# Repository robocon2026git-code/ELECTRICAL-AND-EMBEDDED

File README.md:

\# GITHUB WORKFLOW GUIDE

Welcome to \*\*ROBOCON WORKSPACE\*\*

This document explains \*\*how team members should clone the repo, set up Git, and work using feature branches\*\*.

⚠️ Direct changes to `main` are NOT allowed.  

All work must be done using \*\*feature branches\*\* and merged via \*\*Pull Requests (PRs)\*\*.

---

\## 🧠 Git Basics (Quick Understanding)

\- \*\*Repository (repo)\*\* → Project stored with version control

\- \*\*main branch\*\* → Stable, reviewed code only

\- \*\*feature branch\*\* → Your personal workspace

\- \*\*commit\*\* → A saved snapshot of changes

\- \*\*origin\*\* → Remote GitHub repository

\- \*\*Pull Request (PR)\*\* → Request to merge code into `main`

---

\## One-Time Setup (Required on Every New PC)

Run these commands \*\*once\*\* after installing Git:

```bash

git config --global user.name "Your Name"

git config --global user.email "your-email@example.com"

git config --global init.defaultBranch main

\## To verify configuration

git config --global --list

**## Cloning and work steps starts from here:**

!!!!IMPORTANT ONE TIME SETTING AFTER INSTALLED GIT:

git clone https://github.com/robocon2026git-code/ELECTRICAL-AND-EMBEDDED.git

# \## REGULAR WORK PROCEDURE

1)cd ELECTRO-CORE

2)git status

3)git checkout main					//This line says go to main branch

4)git pull origin main					//Important step otherwise you might miss some files that was updated recently

5)git checkout -b feature/short-description		//Creating your local workspace

    ex:

        git checkout -b feature/pneumatic\_actuation

	git checkout -b feature/arduino-motor

	git checkout -b feature/i2c-driver

After work done run this command once

6)git status

\## THE FOLLOWING STEPS ARE AFTER COMPLETION OF YOUR WORK

\*\* THIS THREE COMMENTS WE WILL USE FREQUENTLY

7)git add .

8)git commit -m "Added new functionality to drive train"

Run this command only when your first push after creation of your feature branch

9) a_)git push -u origin feature/your-branch-name

from next push onwards you can just type

   b_)git push

For local space

10) a_)git branch -d feature/your-branch-name		//Run this comment only after code is merged. This will delete your branch

For remote space

    b_)git push origin --delete feature/your-branch-name

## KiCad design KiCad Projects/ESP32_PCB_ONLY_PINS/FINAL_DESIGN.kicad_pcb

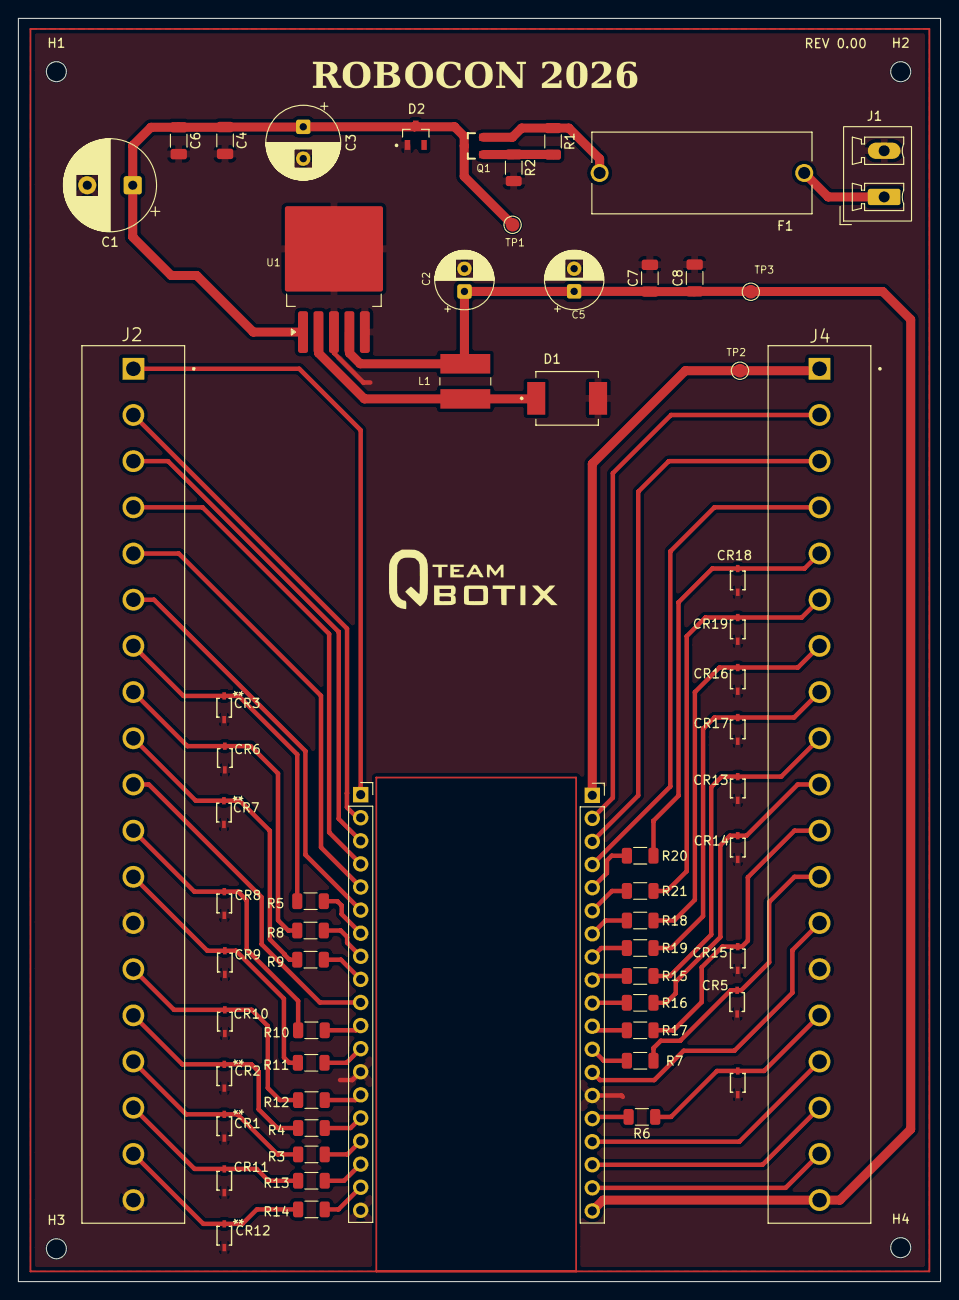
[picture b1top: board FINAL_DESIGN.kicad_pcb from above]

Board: 2 copper layers, 101.4 x 138.9 mm, 66 parts (0 on the bottom side), 60 nets.

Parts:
C1: 680uF; CP_Radial_D10.0mm_P5.00mm
C2, C5: 220uF; CP_Radial_D6.3mm_P2.50mm
C3: 470uF; CP_Radial_D8.0mm_P3.50mm
C4, C7: 10uF; C_1206_3216Metric
C6, C8: 0.1uF; C_1206_3216Metric
CR1, CR2, CR3, CR4, CR5, CR6, CR7, CR8, CR9, CR10, CR11, CR12, CR13, CR14, CR15, CR16, CR17, CR18, CR19: PESD3V3L1BA_115; DIODE_PESD3V3L1BA_115_NEX
D1: SS34; DIO_SS34
D2: MMBZ5242B-7-F; SOT91P240X102-3N
F1: 4628; FUSE_4628
H1, H2, H3, H4: MountingHole_2.2mm_M2
J1: Screw_Terminal_01x02; PhoenixContact_MCV_1,5_2-G-5.08_1x02_P5.08mm_Vertical
J2, J4: TB010-508-P19BK; CUI_TB010-508-P19BK
J3, J5: Conn_01x19_Socket; PinSocket_1x19_P2.54mm_Vertical
L1: WE-PD2_4532; L_Wuerth_WE-PD2-Typ-MS
Q1: AO3401A; SOT23-3
R1, R2: 100K; R_1206_3216Metric
R3, R4: 33; R_1206_3216Metric
R5, R6, R7, R8, R9, R10, R11, R12, R13, R14, R15, R16, R17, R18, R19, R20, R21: 100; R_1206_3216Metric
TP1: 12V; TestPoint_Pad_D1.5mm
TP2: 3V3; TestPoint_Pad_D1.5mm
TP3: 5V; TestPoint_Pad_D1.5mm
U1: LM2596S-5; TO-263-5_TabPin3

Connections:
+3V3: J4.1, J5.1, TP2.1 (1_1)
/12V: C1.1, C3.1, C4.1, C6.1, D2.3, Q1.3, TP1.1 (1_1), U1.1 (VIN)
CLK: J2.1, J3.1
CMD: J4.18, J5.18
EN: J4.2, J5.2
GND: C1.2, C2.2, C3.2, C4.2, C5.2, C6.2, C7.2, C8.2, CR1.2, CR2.2, CR3.2, CR4.2, CR5.2, CR6.2, CR7.2, CR8.2, CR9.2, CR10.2, CR11.2, CR12.2, CR13.2, CR14.2, CR15.2, CR16.2, CR17.2, CR18.2, CR19.2, D1.A, D2.1, J1.2, J2.13, J2.19, J3.13, J3.19, J4.14, J5.14, R2.2, U1.3 (GND), U1.5 (~ON/OFF)
IO_1: J3.16, R3.2
IO_3: J3.15, R4.2
IO_4: J3.7, R5.2
IO_13: J5.15, R6.2
IO_14: J5.12, R7.2
IO_16: J3.8, R8.2
IO_17: J3.9, R9.2
IO_18: J3.11, R10.2
IO_19: J3.12, R11.2
IO_21: J3.14, R12.2
IO_22: J3.17, R13.2
IO_23: J3.18, R14.2
IO_25: J5.9, R15.2
IO_26: J5.10, R16.2
IO_27: J5.11, R17.2
IO_32: J5.7, R18.2
IO_33: J5.8, R19.2
IO_34: J5.5, R20.2
IO_35: J5.6, R21.2
I/O_0: J2.6, J3.6
I/O_2: J2.5, J3.5
I/O_4: CR3.1, J2.7, R5.1
I/O_5: J2.10, J3.10
I/O_12: J4.13, J5.13
I/O_13: CR4.1, J4.15, R6.1
I/O_14: CR5.1, J4.12, R7.1
I/O_15: J2.4, J3.4
I/O_16: CR6.1, J2.8, R8.1
I/O_17: CR7.1, J2.9, R9.1
I/O_18: CR8.1, J2.11, R10.1
I/O_19: CR9.1, J2.12, R11.1
I/O_21: CR10.1, J2.14, R12.1
I/O_22: CR11.1, J2.17, R13.1
I/O_23: CR12.1, J2.18, R14.1
I/O_25: CR13.1, J4.9, R15.1
I/O_26: CR14.1, J4.10, R16.1
I/O_27: CR15.1, J4.11, R17.1
I/O_32: CR16.1, J4.7, R18.1
I/O_33: CR17.1, J4.8, R19.1
I/O_34: CR18.1, J4.5, R20.1
I/O_35: CR19.1, J4.6, R21.1
unnamed: F1.2, Q1.2, R1.1
unnamed: F1.1, J1.1
unnamed: Q1.1, R1.2, R2.1
unnamed: D1.C, L1.1, U1.2 (OUT)
RXD: CR2.1, J2.15, R4.1
SD0: J2.2, J3.2
SD1: J2.3, J3.3
SD2: J4.16, J5.16
SD3: J4.17, J5.17
SN: J4.4, J5.4
SP: J4.3, J5.3
TXD: CR1.1, J2.16, R3.1
VIN 5V: C2.1, C5.1, C7.1, C8.1, J4.19, J5.19, L1.2, TP3.1 (1_1), U1.4 (FB)

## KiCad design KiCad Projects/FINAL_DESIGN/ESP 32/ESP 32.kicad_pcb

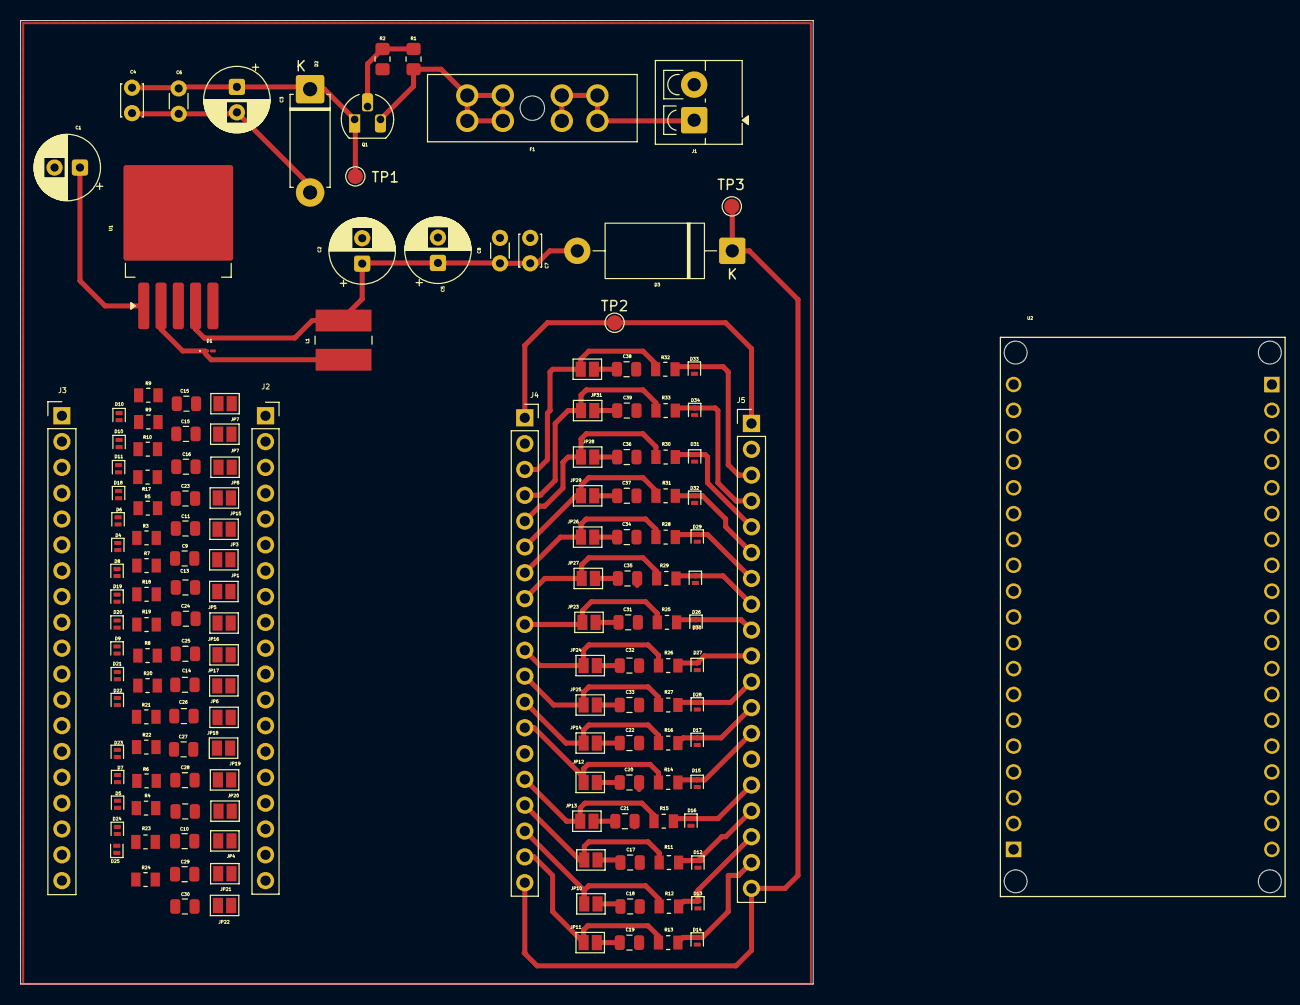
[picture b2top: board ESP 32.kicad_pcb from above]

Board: 2 copper layers, 78.0 x 94.7 mm, 154 parts (0 on the bottom side), 105 nets.

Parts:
C1: 680uF; CP_Radial_D6.3mm_P2.50mm
C2, C5: 220uF; CP_Radial_D6.3mm_P2.50mm
C3: 470uF; CP_Radial_D6.3mm_P2.50mm
C4, C7: 10uF; C_Disc_D3.0mm_W2.0mm_P2.50mm
C6, C8: 0.1uF; C_Disc_D3.0mm_W1.6mm_P2.50mm
C9, C10, C11, C12, C13, C14, C15, C15#2, C16, C17, C18, C19, C20, C21, C22, C23, C24, C25, C26, C27, C28, C29, C30, C31, C32, C33, C34, C35, C36, C37, C38, C39: 100nf; C_0805_2012Metric
D1: 1N5824; D_01005_0402Metric_Pad0.57x0.30mm_HandSolder
D2: D_Zener; D_5W_P10.16mm_Horizontal
D3: Shottky; D_DO-201_P15.24mm_Horizontal
D4, D5, D6, D7, D8, D9, D10, D10#2, D11, D12, D13, D14, D15, D16, D17, D18, D19, D20, D21, D22, D23, D24, D25, D26, D27, D28, D29, D30, D31, D32, D33, D34: D_Zener; D_SOD-882
F1: 3A; FuseHolder_Blade_ATO_Littelfuse_FLR_178.6165
J1: Screw_Terminal_01x02; TerminalBlock_4Ucon_1x02_P3.50mm_Vertical
J2, J4: Conn_01x19_Socket; PinSocket_1x19_P2.54mm_Vertical
J3, J5: Conn_01x19_Socket; PinHeader_1x19_P2.54mm_Vertical
JP1, JP2, JP3, JP4, JP5, JP6, JP7, JP7#2, JP8, JP9, JP10, JP11, JP12, JP13, JP14, JP15, JP16, JP17, JP18, JP19, JP20, JP21, JP22, JP23, JP24, JP25, JP26, JP27, JP28, JP29, JP30, JP31: SolderJumper_2_Open; SolderJumper-2_P1.3mm_Open_Pad1.0x1.5mm
L1: WE-PD2_4532; L_Wuerth_WE-PD2-Typ-MS
Q1: PMOS; TO-92L_HandSolder
R1, R2: 100K; R_0805_2012Metric_Pad1.20x1.40mm_HandSolder
R3, R4, R5, R6, R7, R8, R9, R9#2, R10, R11, R12, R13, R14, R15, R16, R17, R18, R19, R20, R21, R22, R23, R24, R25, R26, R27, R28, R29, R30, R31, R32, R33: 150; RESC2012X60N
TP1: 12V; TestPoint_Pad_D1.5mm
TP2: 3V3; TestPoint_Pad_D1.5mm
TP3: 5V; TestPoint_Pad_D1.5mm
U1: LM2596S-5; TO-263-5_TabPin3
U2: ESP32_NODEMCU; MODULE_ESP32_NODEMCU

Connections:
+3V3: J4.1, J5.1, TP2.1
/5V: C2.1, C5.1, C7.1, C8.1, D3.2 (A), L1.2, U1.4 (FB)
/12V: C1.1, C3.1, C4.1, C6.1, D2.1 (K), Q1.1 (D), TP1.1, U1.1 (VIN)
/CLK: D10.1 (K), J3.1, R9#2.1
/CMD: D14.1 (K), J5.18, R13.1
/EN: J4.2, J5.2
/IO16: JP16.2 (B), R18.2
/IO_0: J2.6, JP1.2 (B), R3.2
/IO_1: J2.16, JP2.2 (B), R4.2
/IO_2: J2.5, JP3.2 (B), R5.2
/IO_3: J2.15, JP4.2 (B), R6.2
/IO_4: J2.7, JP5.2 (B), R7.2
/IO_5: J2.10, JP6.2 (B), R8.2
/IO_6: J2.1, JP7.2 (B), R9#2.2
/IO_7: J2.2, JP7#2.2 (B), R9.2
/IO_8: J2.3, JP8.2 (B), R10.2
/IO_9: J4.16, JP9.2 (B), R11.2
/IO_10: J4.17, JP10.2 (B), R12.2
/IO_11: J4.18, JP11.2 (B), R13.2
/IO_12: J4.13, JP12.2 (B), R14.2
/IO_13: J4.15, JP13.2 (B), R15.2
/IO_14: J4.12, JP14.2 (B), R16.2
/IO_15: J2.4, JP15.2 (B), R17.2
/IO_17: J2.9, JP17.2 (B), R19.2
/IO_18: J2.11, JP18.2 (B), R20.2
/IO_19: J2.12, JP19.2 (B), R21.2
/IO_21: J2.14, JP20.2 (B), R22.2
/IO_22: J2.17, JP21.2 (B), R23.2
/IO_23: J2.18, JP22.2 (B), R24.2
/IO_25: J4.9, JP23.2 (B), R25.2
/IO_26: J4.10, JP24.2 (B), R26.2
/IO_27: J4.11, JP25.2 (B), R27.2
/IO_32: J4.7, JP26.2 (B), R28.2
/IO_33: J4.8, JP27.2 (B), R29.2
/IO_34: J4.5, JP28.2 (B), R30.2
/IO_35: J4.6, JP29.2 (B), R31.2
/IO_36: J4.3, JP30.2 (B), R32.2
/IO_39: J4.4, JP31.2 (B), R33.2
/I/O_0: D4.1 (K), J3.6, R3.1
/I/O_2: D6.1 (K), J3.5, R5.1
/I/O_4: D8.1 (K), J3.7, R7.1
/I/O_5: D9.1 (K), J3.10, R8.1
/I/O_12: D15.1 (K), J5.13, R14.1
/I/O_13: D16.1 (K), J5.15, R15.1
/I/O_14: D17.1 (K), J5.12, R16.1
/I/O_15: D18.1 (K), J3.4, R17.1
/I/O_16: D19.1 (K), J3.8, R18.1
/I/O_17: D20.1 (K), J3.9, R19.1
/I/O_18: D21.1 (K), J3.11, R20.1
/I/O_19: D22.1 (K), J3.12, R21.1
/I/O_21: D23.1 (K), J3.14, R22.1
/I/O_22: D24.1 (K), J3.17, R23.1
/I/O_23: D25.1 (K), J3.18, R24.1
/I/O_25: D26.1 (K), J5.9, R25.1
/I/O_26: D27.1 (K), J5.10, R26.1
/I/O_27: D28.1 (K), J5.11, R27.1
/I/O_32: D29.1 (K), J5.7, R28.1
/I/O_33: D30.1 (K), J5.8, R29.1
/I/O_34: D31.1 (K), J5.5, R30.1
/I/O_35: D32.1 (K), J5.6, R31.1
/RXD: D7.1 (K), J3.15, R6.1
/SD0: D10#2.1 (K), J3.2, R9.1
/SD1: D11.1 (K), J3.3, R10.1
/SD2: D12.1 (K), J5.16, R11.1
/SD3: D13.1 (K), J5.17, R12.1
/SN: D34.1 (K), J5.4, R33.1
/SP: D33.1 (K), J5.3, R32.1
/TXD: D5.1 (K), J3.16, R4.1
GND: C1.2, C2.2, C3.2, C4.2, C5.2, C6.2, C7.2, C8.2, C9.2, C10.2, C11.2, C12.2, C13.2, C14.2, C15.2, C15#2.2, C16.2, C17.2, C18.2, C19.2, C20.2, C21.2, C22.2, C23.2, C24.2, C25.2, C26.2, C27.2, C28.2, C29.2, C30.2, C31.2, C32.2, C33.2, C34.2, C35.2, C36.2, C37.2, C38.2, C39.2, D1.2 (A), D2.2 (A), D4.2 (A), D5.2 (A), D6.2 (A), D7.2 (A), D8.2 (A), D9.2 (A), D10.2 (A), D10#2.2 (A), D11.2 (A), D12.2 (A), D13.2 (A), D14.2 (A), D15.2 (A), D16.2 (A), D17.2 (A), D18.2 (A), D19.2 (A), D20.2 (A), D21.2 (A), D22.2 (A), D23.2 (A), D24.2 (A), D25.2 (A), D26.2 (A), D27.2 (A), D28.2 (A), D29.2 (A), D30.2 (A), D31.2 (A), D32.2 (A), D33.2 (A), D34.2 (A), J1.2, J2.13, J2.19, J3.13, J3.19, J4.14, J5.14, R2.2, U1.3 (GND), U1.5 (~ON/OFF)
unnamed: D1.1 (K), L1.1, U1.2 (OUT)
unnamed: F1.1, J1.1
unnamed: C9.1, JP1.1 (A)
unnamed: C10.1, JP2.1 (A)
unnamed: C11.1, JP3.1 (A)
unnamed: C12.1, JP4.1 (A)
unnamed: C13.1, JP5.1 (A)
unnamed: C14.1, JP6.1 (A)
unnamed: C15.1, C15#2.1, JP7.1 (A), JP7#2.1 (A)
unnamed: C16.1, JP8.1 (A)
unnamed: C17.1, JP9.1 (A)
unnamed: C18.1, JP10.1 (A)
unnamed: C19.1, JP11.1 (A)
unnamed: C20.1, JP12.1 (A)
unnamed: C21.1, JP13.1 (A)
unnamed: C22.1, JP14.1 (A)
unnamed: C23.1, JP15.1 (A)
unnamed: C24.1, JP16.1 (A)
unnamed: C25.1, JP17.1 (A)
unnamed: C26.1, JP18.1 (A)
unnamed: C27.1, JP19.1 (A)
unnamed: C28.1, JP20.1 (A)
unnamed: C29.1, JP21.1 (A)
unnamed: C30.1, JP22.1 (A)
unnamed: C31.1, JP23.1 (A)
unnamed: C32.1, JP24.1 (A)
unnamed: C33.1, JP25.1 (A)
unnamed: C34.1, JP26.1 (A)
unnamed: C35.1, JP27.1 (A)
unnamed: C36.1, JP28.1 (A)
unnamed: C37.1, JP29.1 (A)
unnamed: C38.1, JP30.1 (A)
unnamed: C39.1, JP31.1 (A)
unnamed: Q1.2 (G), R1.2, R2.1
unnamed: F1.2, Q1.3 (S), R1.1
VIN 5V: D3.1 (K), J4.19, J5.19, TP3.1

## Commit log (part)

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2026-01-05 Created Arduino_IDE_Code --> ESP32_Code
2026-01-05 Arduino_IDE_Code folder and child folders added --> ESP32_Code
2026-01-06 Modified code to check
2026-01-08 Added serial.println()
2026-01-08 Added new arduino program check_working
2026-01-08 Deleted Test_arduino code for checking
2026-01-08 Deleted check_working.ino to check
2026-01-08 Added work instruction README.md
2026-01-08 Changed Tittle in README.md
2026-01-08 Generalized tittle given inside README.md
2026-01-12 BOT-2
2026-01-13 Working on design
2026-01-25 Code updated
2026-01-27 Added a section for BLDC Motor
2026-01-27 BLDC Code Added
2026-01-28 locomotion project modified
2026-02-01 Pcb design and stm code_x_lib worked
2026-02-03 stm work
2026-02-03 work
2026-02-05 STM_WORK
2026-02-08 stm & pcb
2026-02-10 worj
2026-02-22 Modified Repo:
2026-02-24 wprk
2026-02-25 pcb update
2026-02-25 pcb work
2026-02-26 track modifiction
2026-02-27 Worked on STM32 Track Locomotion and ESP32 IDF
2026-03-15 Work:
2026-03-25 PCB MODIFIED INSIDE ONLYPINS
2026-03-25 PCB CHANGE
2026-03-26 dtdtdtdt
2026-03-26 Track code modified
2026-03-26 FINAL PCB WORK
2026-03-30 PCB FINAL WORK DONE
2026-04-04 modifications
2026-04-26 stm32 work
2026-05-27 ESP32 R1 Final code
2026-06-03 prajan work
2026-06-08 final bot wrking code
2026-06-08 Old code added
2026-06-22 final changes
